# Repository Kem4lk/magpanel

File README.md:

# FM6363C 80x40 1/20-scan HUB75E panel - ESP32-S3 driver (deneysel port)

mrcodetastic'in **ESP32-PWM-MatrixPanel-DMA** (MBI5153, ESP32-S3) implementasyonunun
FM6363C cipine portu. Panel: P4 indoor 80x40, 1/20 scan, 74HC138 satir decode,
FM6363C S-PWM surucu. Register degerleri panelin fabrika .ssx profilinden alindi.

## Mimari
- **LCD peripheral (DMA)**: DCLK + 6 RGB SDI hatti + LE/LAT -> grayscale verisi ve komutlar
- **GPSPI2 octal (DMA, sonsuz dongu)**: GCLK + A..E adres hatlari (satir tarama)

## Kablolama (mevcut HUB75 baglantin korunuyor)
| HUB75 | Islev | GPIO |
|-------|-------|------|
| R1 G1 B1 | ust yari SDI | 4, 5, 6 |
| R2 G2 B2 | alt yari SDI | 7, 15, 16 |
| A B C D E | satir adresi | 18, 8, 3, 9, 13 |
| CLK | DCLK | 12 |
| LAT | LE (komut) | 10 |
| OE | **GCLK** | 11 |

## Sensörler ve tam bağlantı şeması
`hardware/` klasöründe koddan üretilen şema (`gen_schematic.py` → `schematic.svg/png`) ve
pin tablosu var: [hardware/README.md](hardware/README.md). HUB75 kablolaması değişmedi;
beş JSUMO modülü ESP'nin SAĞ başlığına takılır (hepsi 3V3 ile beslenir):

| Modül | Pin | GPIO |
|-------|-----|------|
| LDR Sensor Board (3 pin, dijital) | DO | 1 (ADC1) |
| Microphone Sound Sensor (3 pin, dijital) | OUT | 42 |
| KY-040 Mechanic Encoder | CLK / DT / SW | 41 / 40 / 39 |
| DHT11 Temperature & Humidity | OUT | 47 |
| TTP223B Digital Touch | SIG | 21 |

Firmware tarafı (`include/sensors.h`, `include/sensor_logic.h`): enkoder = parlaklık,
enkoder/dokunmatik/çift alkış → uyku-uyan / sonraki uygulama / sonraki galeri / oto parlaklık
(web UI "Sensörler & kontroller" kartından eşlenir, NVS'te kalır); LDR ile oto parlaklık;
"Oda" (sıcaklık/nem/ışık/saat) ve "Ses" (VU) uygulamaları; 1 Hz `S:` telemetri + `/api/sensors`.

**KiCad taşıyıcı kart:** ESP32-S3-DevKitC-1 soketi, 2× 74HCT245 DIP-20 (3.3 → 5 V), üç HUB75E
çıkışı ve sensör başlıkları olan 2 katmanlı PCB. Şematik, PCB, gerber ve BOM koddan üretilir:
[hardware/kicad/README.md](hardware/kicad/README.md).

## Derleme
VS Code + PlatformIO eklentisi. Proje klasorunu ac -> Build -> Upload.
(`platformio.ini` ESP32-S3 DevKitC-1 icin hazir.)

## Test asamalari ve sorun giderme
1. **Duz kirmizi/yesil/mavi dolgular**: Temizse config + veri yolu calisiyor demektir.
   - Panel tamamen karanliksa: once `FM_GCLKS_PER_ROW`'u 148 yap (cift-kenar sayim ihtimali),
     olmadi GCLK frekansini dusur (spi_dma_seg_tx_loop.c).
   - Renkler yer degistirmisse: app_constants.hpp'de R/G/B pinlerini duzelt.
2. **Kose pikselleri**: Dort kose dogru yerde ve dogru renkteyse haritalama tamam.
   - Ust/alt yarilar ters ise R1<->R2 gruplarini degistir.
   - Satirlar 2'serli atliyorsa D ve E pinlerini degistir.
3. **Piksel yurutme**: x=0..79 duzgun soldan saga akmiyorsa izledigi sirayi not et:
   - 16'sarlik bloklar ters siradaysa: `FM6363_REVERSE_CHANNEL_ORDER 1` yap.
   - Daha karmasik bir desen varsa fabrika .ssx LookUpTab remap'ini ekleyecegiz (bende cozumu hazir).

## Bilinen belirsizlikler (ilk testte netlesecek)
- GCLK cift-kenar sayimi: 74 vs 148 GCLK/satir denemesi gerekebilir.
- VSYNC sirasinda GCLK duraklatma zamanlamasi hassas olabilir.
- Kanal sirasi (ch15 ilk mi) panel PCB'sine bagli.

## Guncelleme (OTA) ve tek komutla deploy
- Her panel `GITHUB_AUTO_OTA` ile `releases/latest`'teki `version.txt`'i yoklar; build
  numarasi artmissa `firmware.bin`'i indirip kurar. Kurulum sirasinda panelde **tum
  piksellerden olusan, alttan dolan loading ekrani** gosterilir (`drawOtaLoading`).
- "Yukle/deploy" demek icin: `tools/magpanel-mcp/` altindaki MCP sunucusu (repo kokundeki
  `.mcp.json` ile otomatik kayitli). Claude'a **"yukle"** dediginizde `deploy_update` araci
  CI'yi tetikler; firmware `latest` release'e gider ve internete bagli tum paneller otomatik
  guncellenir. Kurulum: [tools/magpanel-mcp/README.md](tools/magpanel-mcp/README.md).

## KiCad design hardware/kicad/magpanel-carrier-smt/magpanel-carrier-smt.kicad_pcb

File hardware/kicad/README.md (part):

# MagPanel Carrier — KiCad 8 şematik + PCB

ESP32-S3-DevKitC-1'i soketle taşıyan, üç HUB75E çıkışı (P4 tek panel ya da P1.86 1–3 modül)
ve beş JSUMO sensör başlığı olan iki katmanlı taşıyıcı kart. Kasa (`enclosure/generate_case.py`)
ve bağlantı şeması (`hardware/gen_schematic.py`) gibi her şey **koddan üretilir**:
[`gen_carrier.py`](gen_carrier.py). Pin, parça ya da yerleşim değişirse dosyanın başındaki
tabloları düzelt ve yeniden üret. KiCad'de elle yapılan değişiklik bir sonraki üretimde kaybolur.

| | |
|---|---|
| Kart | 100 × 63.5 mm, 2 katman, 1.6 mm FR4, köşelerde 4× M3 |
| İz genişliği | sinyal 0.25 mm, 3V3 0.5 mm, 5 V / VIN 0.8–1.0 mm |
| Kurallar | boşluk ≥ 0.15 mm, via 0.6/0.3 mm, kenar 0.3 mm (JLCPCB standart 2 katman) |
| El lehimi | en küçük parça 0805, el lehimi pedleri, parçalar arası ≥ 0.5 mm (DRC kuralı) |
| GND | iki katmanda döküm + dikiş via'ları |
| Doğrulama | ERC 0, DRC 0 ihlal, 0 bağlanmamış, şematik↔PCB farkı 0 |

Doğrulama satırı `fab` aşamasında her seferinde yeniden kontrol edilir. Biri sıfır değilse
gerber üretilmez.

**Evde yapmak için** iki sürüm var. İkisi de Elegoo Saturn 3 Ultra ile pozlanır ve yazıcıya hazır
`.goo` dosyalarıyla gelir: negatif dry film için `saturn3/`, Positiv 20 gibi pozitif lak için
`saturn3-pozitif/`.
- Tek yüz, 150 × 100 mm: yalnız alt bakır, tek pozlama, bakır yüzde 3 tel. DevKit pin adları
  soket sıralarının iç tarafında bakırda yazılı. Anlatım: [`TEK-YUZ.md`](TEK-YUZ.md).
- Çift yüz, 100 × 63.5 mm: kaplamasız delik, SMD'ler altta, 33 telli via. Anlatım:
  [`DIY.md`](DIY.md).
- Yalnız SMD, tek yüz, 150 × 100 mm, **delik yok**: bütün parçalar bakır yüzde; UV lehim maskesi,
  reçine macun stencil'i, yerleştirme şablonu, ısıtıcı tabla. Tel yok, bir 0 Ω köprü. Anlatım:
  [`SMT.md`](SMT.md).

## Dosyalar
| Yol | İçerik |
|---|---|
| `magpanel-carrier/` | KiCad 8 projesi: `.kicad_pro`, `.kicad_sch`, `.kicad_pcb`, `.kicad_dru` |
| `magpanel-carrier/MagPanel.kicad_sym`, `MagPanel.pretty/` | DevKit sembolü ve soket footprint'i |
| `fab/magpanel-carrier-gerber.zip` | gerber + delik dosyaları (doğrudan yüklenir) |
| `fab/magpanel-carrier-bom.csv` | tam malzeme listesi |
| `fab/magpanel-carrier-jlc-bom.csv`, `fab/magpanel-carrier-jlc-cpl.csv` | JLCPCB SMT montajı (yalnız SMD, LCSC numaralı) |
| `fab/magpanel-carrier-robotistan-bom.xlsx`, `fab/magpanel-carrier-robotistan-pnp.xlsx` | Robotistan SMT montajı (yalnız SMD, LCSC numaralı) |
| `fab/magpanel-carrier-bomlist.xlsx` | Türkçe BOM şablonu: Fabrika Kodu, Açıklama, Designatör, Malzeme Kılıfı, Adet (yalnız SMD) |
| `fab/magpanel-carrier-schematic.pdf` | şematik (A3) |
| `fab/magpanel-carrier-1to1.pdf` | 1:1 yerleşim testi (A4, ölçek çubuklu) |
| `magpanel-carrier-ss/`, `fab-ss/` | ev yapımı tek yüz sürüm, 150 × 100 mm, bkz. [`TEK-YUZ.md`](TEK-YUZ.md) |
| `magpanel-carrier-diy/`, `fab-diy/` | ev yapımı çift yüz sürüm, bkz. [`DIY.md`](DIY.md) |
| `magpanel-carrier-smt/`, `fab-smt/` | ev yapımı yalnız SMD sürüm, deliksiz, bkz. [`SMT.md`](SMT.md); kodu `smt_variant.py` |
| `img/` | şematik ve kart görselleri |

Şematik: [`img/schematic.png`](img/schematic.png) · Alt yüz: [`img/pcb-bottom.png`](img/pcb-bottom.png)

## Devre
1. **5 V giriş ve koruma.** Vida klemensi J1, 1.5 A PTC sigorta F1 ve SMAJ5.0A TVS D1'den
   geçer. Ters kutupta D1 iletir ve F1 açar. Ardından 470 µF + 10 µF ile DevKit'in **5V**
   pinine ve tamponlara gider. Panel gücü bu karttan geçmez: PSU'dan panele kalın kablo.
   Kartın kendi tüketimi 1 A'in altındadır.
2. **DevKit soketi U1.** İki adet 1×22 dişi soket. Sağ sıra 1.0" (25.40 mm) uzakta: eldeki
   N16R8 klonu (2× USB-C) 1:1 baskı testinde bu sıraya oturdu. Resmi Espressif kartı 0.9"
   (22.86 mm) kullanır; onun için `DEVKIT_RIGHT_ROWS` değiştirilip yeniden üretilir. Anten
   kartın üst kenarından dışarı taşar, USB alt kenardadır.
3. **Seviye dönüştürücü.** İki CD74HCT245E (DIP-20, soketli), 3.3 V mantığı 5 V'a çevirir
   (DIR = 5 V, /OE = GND). HCT girişleri TTL eşiklidir, 3.3 V yüksek seviyeyi 5 V beslemede
   güvenle okur; düz 74HC245 bu iş için uygun değildir. A pinleri DevKit pinleriyle aynı
   2.54 mm adımda, bir iki satır kayarak kısa ve kesişmeyen izlerle bağlanır.
   LAT, LAT2, LAT3 ve OE'de 10 kΩ pull-down var: açılışta GPIO'lar sürülmezken panel karanlık
   kalır. P4'te OE hattı GCLK taşır, P1.86'da aktif-yüksek OE darbesi.
4. **HUB75E çıkışları J2–J4.** Her hatta bir 33 Ω seri direnç (R10–R25, 0805) kablo
   yansımalarını bastırır. Dirençler tek sütundadır, her biri kendi tampon pininin hizasında.
   Bütün hatlar paraleldir, yalnız LAT panel başına ayrıdır:

   | Konnektör | LAT | Kullanım |
   |---|---|---|
   | J2 PANEL 1 | IO10 | P4 ve P1.86 |
   | J3 PANEL 2 | IO17 | yalnız çoklu P1.86 |
   | J4 PANEL 3 | IO14 | yalnız çoklu P1.86 |

5. **Sensör başlıkları (3.3 V).** Pin sırası eldeki JSUMO modüllerinin baskısıyla aynıdır,
   düz kablo çaprazlamaz. GPIO'lar `include/sensors.h` ile aynıdır, her pin serigrafide yazılıdır.

   | Başlık | Modül baskısı | Kart sırası | GPIO |
   |---|---|---|---|
   | J5 LDR | VCC GND DO | 3V3, GND, DO | DO → IO1 |
   | J6 MIC | OUT GND VCC | DO, GND, 3V3 | OUT → IO42 |
   | J7 ENC | CLK DT SW + GND | CLK, DT, SW, 3V3, GND | IO41 / IO40 / IO39 |
   | J8 DHT | − OUT + | GND, DAT, 3V3 | OUT → IO47 |
   | J9 TOUCH | SIG VCC GND | OUT, 3V3, GND | SIG → IO21 |
   | J10 EXP | | 3V3, GND, IO43, IO44, IO38 | genişleme |

   LDR ve mikrofon modülleri yalnız dijital çıkışlıdır. LDR'nin DO'su IO1'den okunur ve oto
   parlaklık iki kademe çalışır. Mikrofonun OUT'u IO42 kesmesine gider. Analog mikrofon girişi
   IO2 boşta gürültü okumasın diye R7 (10 kΩ) onu GND'ye çeker. C5–C7 enkoder için RC filtre,
   R6 DHT11 veri hattı pull-up'ıdır.

GPIO tablosu ve modül notları: [`../README.md`](../README.md).

## Yeniden üretmek
Gerekenler: KiCad 8 (`pcbnew` python modülü ve `kicad-cli`), Java 21+ (Freerouting için),
görseller için Chromium ya da Chrome (`CHROME=/yol` ile verilebilir).

```bash
cd hardware/kicad
PY=/usr/bin/python3        # Linux: KiCad'in python'u
# macOS: PY=/Applications/KiCad/KiCad.app/Contents/Frameworks/Python.framework/Versions/Current/bin/python3
$PY gen_carrier.py sch     # şematik + proje + semboller (yalnız stdlib)
$PY gen_carrier.py pcb     # yerleşim, kart çerçevesi, kilitli 5 V ana hat, SMD GND via'ları
$PY gen_carrier.py route   # Freerouting 2.1.0 + GND dökümü + dikiş via'ları
$PY gen_carrier.py fab     # ERC/DRC kapısı + gerber/delik/BOM/CPL/PDF + görseller
$PY gen_carrier.py all     # hepsi sırayla
$PY gen_carrier.py --ss all    # ev yapımı tek yüz: magpanel-carrier-ss/ ve fab-ss/ (TEK-YUZ.md)
$PY gen_carrier.py --diy all   # ev yapımı çift yüz: magpanel-carrier-diy/ ve fab-diy/ (DIY.md)
$PY gen_carrier.py --smt all   # yalnız SMD: magpanel-carrier-smt/ ve fab-smt/ (SMT.md)
```

- `route` Freerouting jar'ını yoksa `work/` altına indirir (yaklaşık 67 MB).
- Freerouting deterministik değildir: her çalıştırma farklı ama eşdeğer bir yönlendirme
  verir. Aşama, DRC temiz çıkana kadar en çok 10 kez dener. Freerouting bağlantıyı tamam
  sayıp KiCad kopuk görürse mevcut izlerle bir tamamlama turu daha çalışır.
- `work/` ara dosyalar içindir ve git'e girmez.

## Sipariş ve montaj
- **PCB:** `fab/magpanel-carrier-gerber.zip` yükle. 2 katman, 1.6 mm, HASL ya da ENIG.
- **Önce 1:1 test:** `fab/magpanel-carrier-1to1.pdf` dosyasını yazıcıda %100 ölçekle bas,
  alttaki 100 mm çizgiyi cetvelle doğrula, gerçek parçaları deliklere oturt.
- **SMT montaj (isteğe bağlı):** bütün SMD parçalar üst yüzdedir. Montaj dosyalarında yalnız
  bunlar var (33 parça, 8 satır); delikli parçalar elle lehimlenir. Koordinatlar kartın sol-alt
  köşesine göredir, gerber ve delik dosyaları da aynı orijini kullanır. Parçaların LCSC
  numaraları `gen_carrier.py` içindeki `SMT_PARTS` tablosundadır ve LCSC'de stoklu olarak
  doğrulandı (2026-10-02). Yönler KiCad'den gelir: yerleşim önizlemesinde D1'in katot bandı
  sağda (+5V), D2'nin katodu solda (GND) olmalı.
  - JLCPCB: `jlc-bom.csv` ve `jlc-cpl.csv`.
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
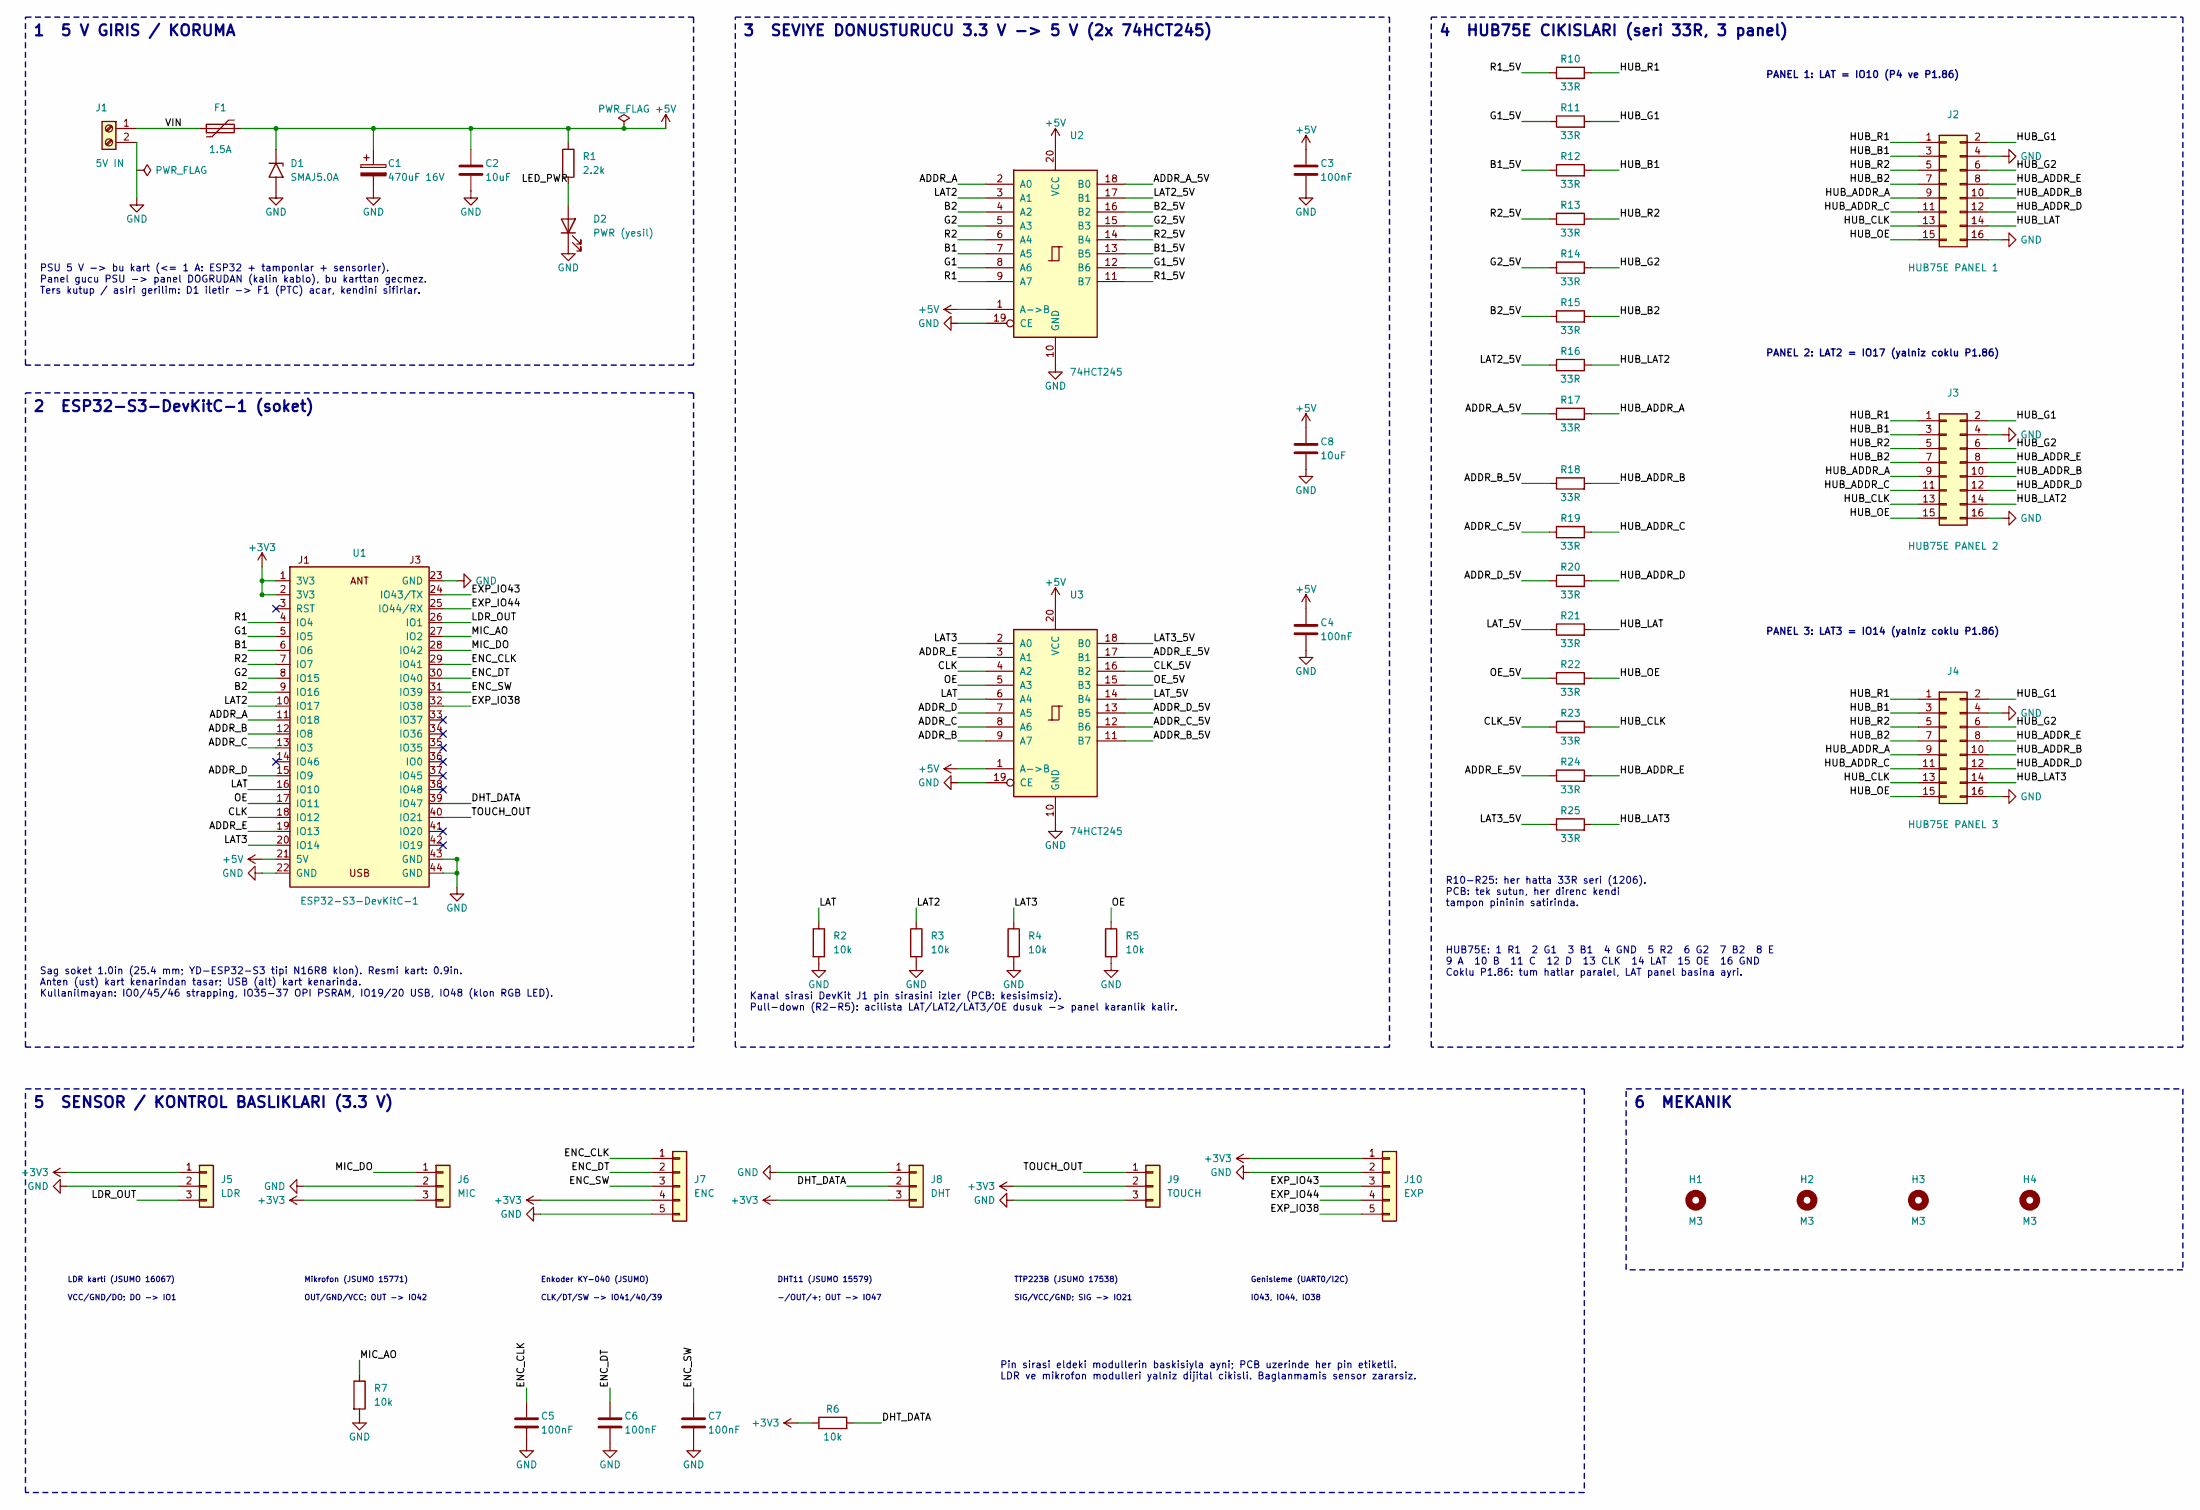
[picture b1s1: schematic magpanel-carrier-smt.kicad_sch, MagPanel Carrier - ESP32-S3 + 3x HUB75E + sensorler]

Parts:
C1: 470uF 16V; CP_Elec_8x10.5; MPN SMD elektrolitik 470 uF 16 V, 8 x 10.5 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
C2, C8: 10uF; C_1206_3216Metric; MPN CL31A106KAHNNNE
C3, C4, C5, C6, C7: 100nF; C_1206_3216Metric; MPN CC1206KRX7R9BB104
D1: SMAJ5.0A; D_SMA; MPN SMAJ5.0A; LCSC C83329
D2: PWR (yesil); LED_1206_3216Metric; MPN KT-1206G
F1: 1.5A; Fuse_1812_4532Metric; MPN MF-MSMF150-2; LCSC C89648
H1, H2, H3, H4: M3; MountMark_M3
J1: 5V IN; BarrelJack_PJ-036AH-SMT; MPN DC jak 5.5 x 2.1 mm SMD (CUI PJ-036AH-S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
J2: HUB75E PANEL 1; IDC-Header_2x08_P2.54mm_Vertical_SMD; MPN SMD kutu baslik (box header) 2x8 2.54 m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
J3: HUB75E PANEL 2; IDC-Header_2x08_P2.54mm_Vertical_SMD; MPN SMD kutu baslik (box header) 2x8 2.54 m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
J4: HUB75E PANEL 3; IDC-Header_2x08_P2.54mm_Vertical_SMD; MPN SMD kutu baslik (box header) 2x8 2.54 m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
J5: LDR; PinHeader_1x03_P2.54mm_SMD; MPN SMD pin header 1x3 2.54 mm erkek
J6: MIC; PinHeader_1x03_P2.54mm_SMD; MPN SMD pin header 1x3 2.54 mm erkek
J7: ENC; PinHeader_1x05_P2.54mm_SMD; MPN SMD pin header 1x5 2.54 mm erkek
J8: DHT; PinHeader_1x03_P2.54mm_SMD; MPN SMD pin header 1x3 2.54 mm erkek
J9: TOUCH; PinHeader_1x03_P2.54mm_SMD; MPN SMD pin header 1x3 2.54 mm erkek
J10: EXP; PinHeader_1x05_P2.54mm_SMD; MPN SMD pin header 1x5 2.54 mm erkek
R1: 2.2k; R_1206_3216Metric; MPN 1206W4J0222T5E
R2, R3, R4, R5, R6, R7: 10k; R_1206_3216Metric; MPN 1206W4J0103T5E
R10, R11, R12, R13, R14, R15, R16, R17, R18, R19, R20, R21, R22, R23, R24, R25: 33R; R_1206_3216Metric; MPN 1206W4J0330T5E
U1: ESP32-S3-DevKitC-1; ESP32-S3-DevKitC-1_SMD; MPN ESP32-S3 N16R8 klon (siralar arasi 1.0i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
U2, U3: 74HCT245; SOIC-20W_7.5x12.8mm_P1.27mm; MPN SN74HCT245DWR / 74HCT245D (SOIC-20W)

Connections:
+3V3: J5.1, J6.3, J7.4, J8.3, J9.2, J10.1, R6.1, U1.1 (3V3), U1.2 (3V3); also elsewhere on the board
+5V: C1.1, C2.1, C3.1, C4.1, C8.1, D1.1 (A1), F1.2, R1.1, U1.21 (5V), U2.1 (A->B), U2.20 (VCC), U3.1 (A->B), U3.20 (VCC)
/ADDR_A: U1.11 (IO18), U2.2 (A0)
/ADDR_A_5V: R17.1, U2.18 (B0)
/ADDR_B: U1.12 (IO8), U3.9 (A7)
/ADDR_B_5V: R18.1, U3.11 (B7)
/ADDR_C: U1.13 (IO3), U3.8 (A6)
/ADDR_C_5V: R19.1, U3.12 (B6)
/ADDR_D: U1.15 (IO9), U3.7 (A5)
/ADDR_D_5V: R20.1, U3.13 (B5)
/ADDR_E: U1.19 (IO13), U3.3 (A1)
/ADDR_E_5V: R24.1, U3.17 (B1)
/B1: U1.6 (IO6), U2.7 (A5)
/B1_5V: R12.1, U2.13 (B5)
/B2: U1.9 (IO16), U2.4 (A2)
/B2_5V: R15.1, U2.16 (B2)
/CLK: U1.18 (IO12), U3.4 (A2)
/CLK_5V: R23.1, U3.16 (B2)
/DHT_DATA: J8.2, R6.2, U1.39 (IO47)
/ENC_CLK: C5.1, J7.1, U1.29 (IO41)
/ENC_DT: C6.1, J7.2, U1.30 (IO40)
/ENC_SW: C7.1, J7.3, U1.31 (IO39)
/EXP_IO38: J10.5, U1.32 (IO38)
/EXP_IO43: J10.3, U1.24 (IO43/TX)
/EXP_IO44: J10.4, U1.25 (IO44/RX)
/G1: U1.5 (IO5), U2.8 (A6)
/G1_5V: R11.1, U2.12 (B6)
/G2: U1.8 (IO15), U2.5 (A3)
/G2_5V: R14.1, U2.15 (B3)
/HUB_ADDR_A: J2.9, J3.9, J4.9, R17.2
/HUB_ADDR_B: J2.10, J3.10, J4.10, R18.2
/HUB_ADDR_C: J2.11, J3.11, J4.11, R19.2
/HUB_ADDR_D: J2.12, J3.12, J4.12, R20.2
/HUB_ADDR_E: J2.8, J3.8, J4.8, R24.2
/HUB_B1: J2.3, J3.3, J4.3, R12.2
/HUB_B2: J2.7, J3.7, J4.7, R15.2
/HUB_CLK: J2.13, J3.13, J4.13, R23.2
/HUB_G1: J2.2, J3.2, J4.2, R11.2
/HUB_G2: J2.6, J3.6, J4.6, R14.2
/HUB_LAT: J2.14, R21.2
/HUB_LAT2: J3.14, R16.2
/HUB_LAT3: J4.14, R25.2
/HUB_OE: J2.15, J3.15, J4.15, R22.2
/HUB_R1: J2.1, J3.1, J4.1, R10.2
/HUB_R2: J2.5, J3.5, J4.5, R13.2
/LAT: R2.1, U1.16 (IO10), U3.6 (A4)
/LAT2: R3.1, U1.10 (IO17), U2.3 (A1)
/LAT2_5V: R16.1, U2.17 (B1)
/LAT3: R4.1, U1.20 (IO14), U3.2 (A0)
/LAT3_5V: R25.1, U3.18 (B0)
/LAT_5V: R21.1, U3.14 (B4)
/LDR_OUT: J5.3, U1.26 (IO1)
/LED_PWR: D2.2 (A), R1.2
/MIC_AO: R7.1, U1.27 (IO2)
/MIC_DO: J6.1, U1.28 (IO42)
/OE: R5.1, U1.17 (IO11), U3.5 (A3)
/OE_5V: R22.1, U3.15 (B3)
/R1: U1.4 (IO4), U2.9 (A7)
/R1_5V: R10.1, U2.11 (B7)
/R2: U1.7 (IO7), U2.6 (A4)
/R2_5V: R13.1, U2.14 (B4)
/TOUCH_OUT: J9.1, U1.40 (IO21)
/VIN: F1.1, J1.1
GND: C1.2, C2.2, C3.2, C4.2, C5.2, C6.2, C7.2, C8.2, D1.2 (A2), D2.1 (K), J1.2, J2.4, J2.16, J3.4, J3.16, J4.4, J4.16, J5.2, J6.2, J7.5, J8.1, J9.3, J10.2, R2.2, R3.2, R4.2, R5.2, R7.2, U1.22 (GND), U1.23 (GND), U1.43 (GND), U1.44 (GND), U2.10 (GND), U2.19 (CE), U3.10 (GND), U3.19 (CE)

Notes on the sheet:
1 5 V GIRIS / KORUMA
PSU 5 V -> bu kart (<= 1 A: ESP32 + tamponlar + sensorler). Panel gucu PSU -> panel DOGRUDAN (kalin kablo), bu karttan gecmez. Ters kutup / asiri gerilim: D1 iletir -> F1 (PTC) acar, kendini sifirlar.
2 ESP32-S3-DevKitC-1 (soket)
Sag soket 1.0in (25.4 mm; YD-ESP32-S3 tipi N16R8 klon). Resmi kart: 0.9in. Anten (ust) kart kenarindan tasar; USB (alt) kart kenarinda. Kullanilmayan: IO0/45/46 strapping, IO35-37 OPI PSRAM, IO19/20 USB, IO48 (klon RGB LED).
3 SEVIYE DONUSTURUCU 3.3 V -> 5 V (2x 74HCT245)
Kanal sirasi DevKit J1 pin sirasini izler (PCB: kesisimsiz). Pull-down (R2-R5): acilista LAT/LAT2/LAT3/OE dusuk -> panel karanlik kalir.
4 HUB75E CIKISLARI (seri 33R, 3 panel)
R10-R25: her hatta 33R seri (1206). PCB: tek sutun, her direnc kendi tampon pininin satirinda.
PANEL 1: LAT = IO10 (P4 ve P1.86)
PANEL 2: LAT2 = IO17 (yalniz coklu P1.86)
PANEL 3: LAT3 = IO14 (yalniz coklu P1.86)
HUB75E: 1 R1 2 G1 3 B1 4 GND 5 R2 6 G2 7 B2 8 E 9 A 10 B 11 C 12 D 13 CLK 14 LAT 15 OE 16 GND Coklu P1.86: tum hatlar paralel, LAT panel basina ayri.
5 SENSOR / KONTROL BASLIKLARI (3.3 V)
LDR karti (JSUMO 16067)
VCC/GND/DO; DO -> IO1
Mikrofon (JSUMO 15771)
OUT/GND/VCC; OUT -> IO42
Enkoder KY-040 (JSUMO)
CLK/DT/SW -> IO41/40/39
DHT11 (JSUMO 15579)
-/OUT/+; OUT -> IO47
TTP223B (JSUMO 17538)
SIG/VCC/GND; SIG -> IO21
Genisleme (UART0/I2C)
IO43, IO44, IO38
Pin sirasi eldeki modullerin baskisiyla ayni; PCB uzerinde her pin etiketli. LDR ve mikrofon modulleri yalniz dijital cikisli. Baglanmamis sensor zararsiz.
6 MEKANIK

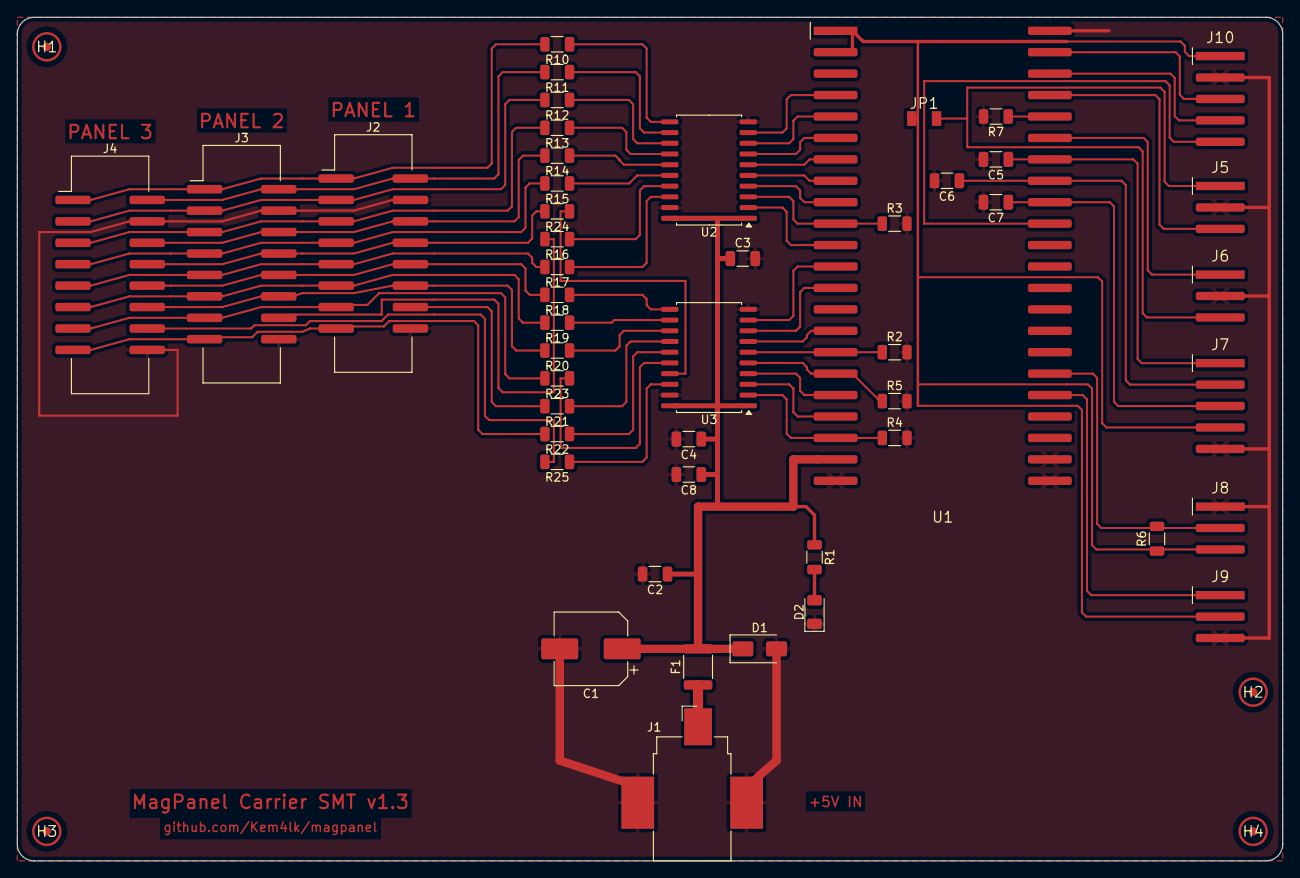
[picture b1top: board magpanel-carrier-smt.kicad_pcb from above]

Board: 2 copper layers, 150.0 x 100.0 mm, 52 parts (0 on the bottom side), 64 nets.

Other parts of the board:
JP1: 0R; Bridge_0R_1206

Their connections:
+3V3: JP1.1, JP1.2; also elsewhere on the board

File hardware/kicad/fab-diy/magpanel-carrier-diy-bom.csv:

Ref,Adet,Deger,Footprint,Montaj,Uretici,Parca / MPN,LCSC,Not
C1,1,470uF 10V,CP_Radial_D8.0mm_P3.50mm,THT,,"Elektrolitik 470 uF 10 V, D8 P3.5 (low ESR)",,"5 V giris tamponu (kablo enduktansi, tampon anahtarlama akimlari)"
C2,1,10uF,C_0805_2012Metric_Pad1.18x1.45mm_HandSolder,SMD,Samsung,CL21A106KAYNNNE,C15850,5 V giris seramik dekuplaj
C3 C4,2,100nF,C_0805_2012Metric_Pad1.18x1.45mm_HandSolder,SMD,YAGEO,CC0805KRX7R9BB104,C49678,74HCT245 VCC dekuplaj (pin 20 yaninda)
C5 C6 C7,3,100nF,C_0805_2012Metric_Pad1.18x1.45mm_HandSolder,SMD,YAGEO,CC0805KRX7R9BB104,C49678,Enkoder RC debounce (modul 10k + 100nF ~ 1 ms)
C8,1,10uF,C_0805_2012Metric_Pad1.18x1.45mm_HandSolder,SMD,Samsung,CL21A106KAYNNNE,C15850,Tamponlar icin yerel 5 V yigin kapasitesi
D1,1,SMAJ5.0A,D_SMA_Handsoldering,SMD,Littelfuse,SMAJ5.0A,C83329,TVS: ters kutup/asiri gerilimde iletir -> F1 acar
D2,1,PWR (yesil),LED_0805_2012Metric_Pad1.15x1.40mm_HandSolder,SMD,Hubei KENTO,KT-0805G,C2297,5 V var gostergesi
F1,1,1.5A,Fuse_1812_4532Metric_Pad1.30x3.40mm_HandSolder,SMD,BOURNS,MF-MSMF150-2,C89648,Kendini sifirlayan sigorta: asiri akim / ters kutupta (D1 iletir) acar
J1,1,5V IN,"TerminalBlock_Phoenix_MKDS-1,5-2-5.08_1x02_P5.08mm_Horizontal",THT,,"Phoenix MKDS 1,5/2-5,08 (1714955) ya da esdegeri",,5 V DC giris (PSU). Panel gucu PSU -> panel dogrudan; bu kart <= 1 A ceker.
J2,1,HUB75E PANEL 1,IDC-Header_2x08_P2.54mm_Vertical,THT,,"Kutu baslik (box header) 2x8 2.54 mm, duz",,HUB75E panel cikisi: LAT = IO10 (P4 ve P1.86)
J3,1,HUB75E PANEL 2,IDC-Header_2x08_P2.54mm_Vertical,THT,,"Kutu baslik (box header) 2x8 2.54 mm, duz",,HUB75E panel cikisi: LAT2 = IO17 (yalniz coklu P1.86)
J4,1,HUB75E PANEL 3,IDC-Header_2x08_P2.54mm_Vertical,THT,,"Kutu baslik (box header) 2x8 2.54 mm, duz",,HUB75E panel cikisi: LAT3 = IO14 (yalniz coklu P1.86)
J5,1,LDR,PinHeader_1x03_P2.54mm_Vertical,THT,,Pin header 1x3 2.54 mm erkek (Dupont),,LDR karti (JSUMO 16067) - VCC/GND/DO; DO -> IO1
J6,1,MIC,PinHeader_1x03_P2.54mm_Vertical,THT,,Pin header 1x3 2.54 mm erkek (Dupont),,Mikrofon (JSUMO 15771) - OUT/GND/VCC; OUT -> IO42
J7,1,ENC,PinHeader_1x05_P2.54mm_Vertical,THT,,Pin header 1x5 2.54 mm erkek (Dupont),,Enkoder KY-040 (JSUMO) - CLK/DT/SW -> IO41/40/39
J8,1,DHT,PinHeader_1x03_P2.54mm_Vertical,THT,,Pin header 1x3 2.54 mm erkek (Dupont),,DHT11 (JSUMO 15579) - -/OUT/+; OUT -> IO47
J9,1,TOUCH,PinHeader_1x03_P2.54mm_Vertical,THT,,Pin header 1x3 2.54 mm erkek (Dupont),,TTP223B (JSUMO 17538) - SIG/VCC/GND; SIG -> IO21
J10,1,EXP,PinHeader_1x05_P2.54mm_Vertical,THT,,Pin header 1x5 2.54 mm erkek (Dupont),,"Genisleme (UART0/I2C) - IO43, IO44, IO38"
R1,1,2.2k,R_0805_2012Metric_Pad1.20x1.40mm_HandSolder,SMD,UNI-ROYAL,0805W8F2201T5E,C17520,PWR LED akim siniri (~1 mA)
R2 R3 R4 R5,4,10k,R_0805_2012Metric_Pad1.20x1.40mm_HandSolder,SMD,UNI-ROYAL,0805W8F1002T5E,C17414,Pull-down: acilista GPIO surulmezken LAT/OE dusuk -> panel karanlik
R6,1,10k,R_0805_2012Metric_Pad1.20x1.40mm_HandSolder,SMD,UNI-ROYAL,0805W8F1002T5E,C17414,DHT11 DATA pull-up (ciplak sensor icin; modul uzerindekiyle paralel sorun degil)
R7,1,10k,R_0805_2012Metric_Pad1.20x1.40mm_HandSolder,SMD,UNI-ROYAL,0805W8F1002T5E,C17414,IO2 (analog mikrofon girisi) bosta gurultu okumasin: eldeki mikrofon modulu yalniz dijital
R10 R11 R12 R13 R14 R15 R16 R17 R18 R19 R20 R21 R22 R23 R24 R25,16,33R,R_0805_2012Metric_Pad1.20x1.40mm_HandSolder,SMD,UNI-ROYAL,0805W8F330JT5E,C17634,Seri sonlandirma: kablo yansimalarini/zil (ringing) bastirir
U1,1,ESP32-S3-DevKitC-1,ESP32-S3-DevKitC-1_Socket,THT,,"ESP32-S3 N16R8 klon (YD-ESP32-S3 tipi, siralar arasi 1.0in) + 2x 1x22 disi soket (2.54 mm)",,"ESP32-S3-DevKitC-1 uyumlu gelistirme karti (eldeki: N16R8 klon, 2x USB-C); 2x22 disi soket. Sag sira 1.0in (25.4 mm); resmi Espressif karti 0.9in."
U2 U3,2,74HCT245,DIP-20_W7.62mm_Socket_LongPads,THT,,CD74HCT245E (PDIP-20) + 20 pin DIP soket,,"Octal bus transceiver, HCT = TTL girisli (3.3 V mantik 5 V beslemede gecerli); DIR=+5V (A->B), /OE=GND"

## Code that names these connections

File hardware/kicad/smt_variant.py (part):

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    for y in (y34b, g(6) - 0.17):
        out.append(('+3V3', [(xin, y), (xo, y)], 0.25))
    # IO38 halkası
    out.append(('EXP_IO38', [(xi, pin_y(10)), (IO38_X, pin_y(10)), (IO38_X, y34a), (xo, y34a)], W))
    # dış taraf: sağ sıra -> başlıklar (merdiven, sağa)
    hp = lambda ref, k: pad(ref, str(k))
    tx = SENS_X - 2.3
    sens = [('+3V3', g(1), hp('J10', 1)), ('EXP_IO43', pin_y(2), hp('J10', 3)), ('EXP_IO44', pin_y(3), hp('J10', 4)),
            ('EXP_IO38', y34a, hp('J10', 5)), ('+3V3', y34b, hp('J5', 1)), ('LDR_OUT', pin_y(4), hp('J5', 3)),
            ('MIC_DO', pin_y(6), hp('J6', 1)), ('+3V3', g(6) - 0.17, hp('J6', 3)), ('ENC_CLK', pin_y(7), hp('J7', 1)),
            ('ENC_DT', pin_y(8), hp('J7', 2)), ('ENC_SW', pin_y(9), hp('J7', 3)), ('+3V3', yb[0], hp('J7', 4)),
            ('DHT_DATA', pin_y(17), hp('J8', 2)), ('+3V3', yb[1], hp('J8', 3)), ('TOUCH_OUT', pin_y(18), hp('J9', 1)),
            ('+3V3', yb[2], hp('J9', 2))]
    lines = [('%d' % k, (xo, y), (tx, t[1])) for k, (n, y, t) in enumerate(sens)]
    # LDR-MIC, CLK-DT, DT-SW, SW-3V3 arasında döküm geçer: IO38 halkasının içindeki R7, C5-C7 GND'si buradan
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
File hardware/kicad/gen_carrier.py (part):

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        return str(DEVKIT_J1.index(name) + 1)
    return str(DEVKIT_J3.index(name) + 23)

# HUB75: ESP GPIO -> sinyal (include/app_constants.hpp; LAT2/LAT3 panel_sm16380.h)
HUB_GPIO = {
    'R1': 'IO4', 'G1': 'IO5', 'B1': 'IO6', 'R2': 'IO7', 'G2': 'IO15', 'B2': 'IO16',
    'ADDR_A': 'IO18', 'ADDR_B': 'IO8', 'ADDR_C': 'IO3', 'ADDR_D': 'IO9', 'ADDR_E': 'IO13',
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# pin 1 tampon tarafi (*_5V), pin 2 konnektor tarafi (HUB_*). (ref, sinyal, DevKit satiri)
SERIES_R = ([('R%d' % (10 + k), sig, 2 + k) for k, sig in enumerate(reversed(BUF_CH['U2']))] +
            [('R%d' % (18 + k), sig, 13 + k) for k, sig in enumerate(reversed(BUF_CH['U3']))])
# HUB75E konnektor pinleri (standart). 14 = LAT (panel basina ayri).
HUB_PINS = {1: 'R1', 2: 'G1', 3: 'B1', 4: 'GND', 5: 'R2', 6: 'G2', 7: 'B2', 8: 'ADDR_E',
            9: 'ADDR_A', 10: 'ADDR_B', 11: 'ADDR_C', 12: 'ADDR_D', 13: 'CLK', 14: None,
            15: 'OE', 16: 'GND'}
HUB_CONN = [('J2', 'LAT', 'PANEL 1', 'LAT = IO10 (P4 ve P1.86)'),
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    ('J9', 'TOUCH', [('OUT', 'TOUCH_OUT'), ('3V3', '+3V3'), ('GND', 'GND')], 'TTP223B (JSUMO 17538) - SIG/VCC/GND; SIG -> IO21'),
    ('J10', 'EXP', [('3V3', '+3V3'), ('GND', 'GND'), ('IO43', 'EXP_IO43'), ('IO44', 'EXP_IO44'), ('IO38', 'EXP_IO38')], 'Genisleme (UART0/I2C) - IO43, IO44, IO38'),
]
SENSOR_GPIO = {'LDR_OUT': 'IO1', 'MIC_AO': 'IO2', 'MIC_DO': 'IO42', 'ENC_CLK': 'IO41', 'ENC_DT': 'IO40',
               'ENC_SW': 'IO39', 'DHT_DATA': 'IO47', 'TOUCH_OUT': 'IO21', 'EXP_IO43': 'IO43/TX',
               'EXP_IO44': 'IO44/RX', 'EXP_IO38': 'IO38'}
ENC_CAPS = [('C5', 'ENC_CLK'), ('C6', 'ENC_DT'), ('C7', 'ENC_SW')]
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                   desc='5 V var gostergesi')
    ra = r1.pin(2); la = d2.pin(2)
    sch.wire((ra[0], ra[1]), (la[0], la[1]))
    sch.label('LED_PWR', ra[0], ra[1], (-1, 0))
    sch.assign(r1, 2, 'LED_PWR'); sch.assign(d2, 2, 'LED_PWR')
    sch.pwr(d2, 1, 'GND', length=0)
    sch.text('PSU 5 V -> bu kart (<= 1 A: ESP32 + tamponlar + sensorler).\n'
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    for i, (ref, net) in enumerate(PULLDOWNS):
        r = sch.place('Device:R', ref, '10k', *P(63 + i * 7, 72.5), footprint=FP['R0805'],
                      ref_at=(2.54, -1.27), val_at=(2.54, 1.27), fields=smt('10k'),
                      desc='Pull-down: acilista GPIO surulmezken LAT/OE dusuk -> panel karanlik')
        x0, y0, _ = r.pin('1')
        sch.wire((x0, y0), (x0, y0 - G))
        sch.label(net, x0, y0 - G, (1, 0))
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                   desc='IO2 (analog mikrofon girisi) bosta gurultu okumasin: eldeki mikrofon modulu yalniz dijital')
    x0, y0, _ = r7.pin('1')
    sch.wire((x0, y0), (x0, y0 - G))
    sch.label('MIC_AO', x0, y0 - G, (1, 0))
    sch.assign(r7, '1', 'MIC_AO')
    sch.pwr(r7, '2', 'GND', length=0)
    r6 = sch.place('Device:R', 'R6', '10k', *P(64, 107), rot=90, footprint=FP['R0805'],
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    for ref, lat, title, note in HUB_CONN:
        x, y, _, _ = PLACE[ref]
        silk_text(board, '%s %s' % (ref, title), x + 1.27, y - 6.6, 0.9)
        silk_text(board, lat + '=' + HUB_GPIO[lat], x + 1.27, y + 24.2, 0.8)
    # sensor basliklari: ad ustte, pin etiketleri solda
    for ref, name, pins, _ in SENSOR_HDRS:
        x, y, _, _ = PLACE[ref]
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SS_SENS_X = 136.0                 # sensor basliklari (dikey, pin 1 ustte): sinyal + 3V3 soldan, GND sagdan
SS_VIA = (1.6, 0.8)               # tel pedi / delik (tel ucu bakir yuzde pede lehimlenir, delmek istege bagli)
SS_VIA_COST = int(os.environ.get('SS_VIA_COST', 120))   # Freerouting via maliyeti: yuksek -> az tel
# Seri 33R sutunu HUB75 serit sirasinda (... D, CLK, LAT, OE). CLK'nin B pini (satir 18) LAT ve OE'nin altinda:
# iz soketin ic koridorundan yukari cikip D ile LAT arasindan sutuna girer (tel gerekmez).
SS_RROW = {'CLK': 16, 'LAT': 17, 'OE': 18}

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    Basliklar 1.27 mm basamakli: baslik arasi izler duz. Seritte sira pin sirasi (1 R1 ... 16 GND); GND (4, 16) son
    basligin otesinde birlesir. Tek katmanda kesismesi kacinilmaz uc hat telle (ust katman = bakir yuzde tel):
    E (sutunun altindan seritteki yerine), LAT2 (seritin icinden J2-J3 arasina), LAT3 (seritin altindan J3-J4
    arasina). Tampon B pinleri -> 33R; CLK soketin ic koridorundan cikip D ile LAT arasindan sutuna girer."""
    import pcbnew
    w, h2 = 0.25, G / 2
    hubs = ['J2', 'J3', 'J4']                          # tamponlara en yakindan en uzaga
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    T = lambda n, pts, layer=pcbnew.B_Cu, width=w: add_track(board, nets[n], pts, width, layer=layer)
    via = lambda n, x, y: add_via(board, nets[n], x, y, SS_VIA[0], SS_VIA[1])
    hubnet = lambda p: 'GND' if HUB_PINS[p] == 'GND' else 'HUB_' + HUB_PINS[p]
    # 1) basliklar arasi ve baslik ici gecis (LAT = pin 14 panel basina ayri, burada yok)
    for p in range(1, 17):
        if p == 14:
            continue
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    # 2) seri 33R (ped 2) -> J2: 45 derece yelpaze, hepsi J2'nin 2 mm onunde duzlesir
    rref = {sig: ref for ref, sig, _ in SERIES_R}
    slot = {sig: p for p, sig in HUB_PINS.items() if sig not in (None, 'GND')}
    slot['LAT'] = 14
    xe = X['J2'] + G + 2.0
    def into_j2(p):                                    # J2'nin onunden pine (tek pin yakin sutun araligindan)
        r = (p - 1) // 2
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    for v in (l3a, l3b):
        via('HUB_LAT3', *v)
    T('HUB_LAT3', [l3a, l3b], layer=pcbnew.F_Cu)
    # 6) tampon B pinleri -> 33R ped 1 (sutun serit sirasinda; LAT ve OE bir satir asagi, CLK soket icinden)
    for ref, sig, brow in SERIES_R:
        u, pin = ('U2', str(brow + 9)) if brow <= 9 else ('U3', str(brow - 2))   # 180 derece: B pin m satir m-9 / m+2
        xb, yb = pad_xy(fps[u], pin)
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        xr, yrr = pad_xy(fps[ref], '1')
        n = sig + '_5V'
        if sig == 'CLK':
            yg = pin_y(brow - 3) + h2                    # D (satir 15) ile LAT (16) B pinleri arasi
            T(n, [(xb, yb), (xb + 1.85, yb), (xb + 1.85, yg), (xr + (yrr - yg), yg), (xr, yrr)])
        elif abs(yrr - yb) < 1e-6:
            T(n, [(xb, yb), (xr, yrr)])
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
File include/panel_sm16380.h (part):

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    (varsayilan 13) yazilir, ustteki bitler 0.

  COKLU PANEL (1..3, ayni ESP32): modulde OUT soketi yok -> zincir yok. Tum paneller
  ayni RGB/DCLK/OE/ABCDE hatlarini paylasir; sadece LE (LAT, HUB75 pin 14) panel
  basina ayri GPIO'dan gelir (P1: GPIO10 = d6, P2: GPIO17 = d13, P3: GPIO14 = d14).
  Veri paylasilan hatta panel panel ardisik akar; bir panelin gri ton verisini yalniz
  kendi LE'si latch'ler, digerleri ayni bitleri kaydirip gecirir ama latch'lemez.
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static_assert(DATA_WORDS % CYCLE_WORDS == 0, "panel verisi tam cevrim olmali (paneller ardisik)");
static_assert(DATA_WORDS % PASS_WORDS == 0, "panel verisi tam gecis olmali");

// Coklu panel: panel basina LE (LAT) hatti. P1 = BIT_LAT (d6, GPIO10, P4 ile ayni kablo).
constexpr int MAX_PANELS = 3;
constexpr int8_t LAT2_PIN = 17;             // d13: 2. panelin HUB75 pin 14'u
constexpr int8_t LAT3_PIN = 14;             // d14: 3. panelin HUB75 pin 14'u
constexpr uint16_t B_LAT2 = (1 << 13);
constexpr uint16_t B_LAT3 = (1 << 14);
enum Layout : uint8_t { LAYOUT_VERTICAL = 0, LAYOUT_HORIZONTAL = 1 };
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    bus_cfg.pin_d3 = MBI_G2;  bus_cfg.pin_d4 = MBI_B2;  bus_cfg.pin_d5 = MBI_R2;
    bus_cfg.pin_d6 = MBI_LAT;
    bus_cfg.pin_d7 = MBI_GCLK;      // HUB75 OE pini
    bus_cfg.pin_d8 = ADDR_A_PIN;  bus_cfg.pin_d9 = ADDR_B_PIN;  bus_cfg.pin_d10 = ADDR_C_PIN;
    bus_cfg.pin_d11 = ADDR_D_PIN; bus_cfg.pin_d12 = ADDR_E_PIN;
    // 2. ve 3. panelin LE hatlari (baglanmamis olsa da surulur: sabit 0)
    bus_cfg.pin_d13 = n_ >= 2 ? LAT2_PIN : -1;
    bus_cfg.pin_d14 = n_ >= 3 ? LAT3_PIN : -1;
    bus_cfg.pin_d15 = -1;
    bus_.config(bus_cfg);
    bus_.setup_lcd_dma_periph();
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
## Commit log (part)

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2026-06-12 v21
    hello v21
2026-06-12 v22 3 files
2026-06-13 sat jun 13 11:00
2026-06-13 main ccp
2026-06-13 main cpp update
2026-06-13 platform update
2026-06-13 web page ve wifi update
2026-06-13 CI: etiket sabitleme adimini hatasiz birak (release pipeline'i bozmasin)
    continue-on-error: latest etiketi itilemezse bile derleme ve release
    adimlari calismaya devam eder.
    https://claude.ai/code/session_01729z8mfuzpDVT8xM73TWmN
2026-06-13 BLE provisioning + local build OTA fix
    - Local builds (FW_BUILD=0) no longer auto-OTA; prevents boot loop when
    CI firmware has wrong WiFi password after a credential change
    - BLE provisioning: if WiFi fails at boot, panel advertises as
    'MagPanel-Setup' over BLE; use nRF Connect to write 'SSID\nPASS' to
    the CRED characteristic; credentials saved to NVS, panel restarts
    - NVS credential priority: NVS (BLE-stored) > compiled wifi_config.h > BLE mode
2026-06-13 Replace BLE provisioning with WiFi AP-mode (fixes matrix DMA crash)
    BLE library reserved enough internal RAM that the HUB75 DMA buffer
    allocation in Matrix::initMatrix() failed (assert dma_grey_gpio_data
    != nullptr) -> boot loop. BLE + WiFi + large LED DMA do not fit
    together on this chip.
    Switch to WiFi AP-mode provisioning instead: on WiFi failure the panel
    serves an open 'MagPanel-Setup' network; user connects, opens
2026-06-13 Add CLAUDE.md with project working notes and open issues
    Captures: secrets/branch constraints, low-heap (~7KB max block) limit,
    fixed bugs (FW_BUILD==0 OTA guard, BLE->AP-mode DMA crash), the open GIF
    web-page JS error with diagnosis steps, flashing workflows (USB/espota/
    web-update), local env quirks (broken ~/.git, apostrophe path, IP hopping
    needing a DHCP reservation), and the WS protocol. No secrets included.
    https://claude.ai/code/session_01729z8mfuzpDVT8xM73TWmN
2026-06-13 index sayfasini PROGMEM'den akitarak gonder (art/ws "is not defined" fix)
    Sorun: "/" handler'i sayfayi FPSTR ile ~9 KB'lik tek bir heap String'e
    kopyalayip (replace + send) gonderiyordu. Bellek baskisi/parcalanma altinda
    yanit yarim gidebiliyor; govde (butonlar) gorunuyor ama sondaki <script>
    blogu kesiliyor. Eksik script parse edilemiyor -> hicbir global tanimlanmiyor
    -> inline handler'lar "art is not defined" / "ws is not defined" firlatiyor.
    (Sayfa HTML/JS'i tam haliyle gecerli; node --check ve jsdom ile dogrulandi.)
2026-06-13 OTA piksel loading ekrani + tek komutla deploy MCP sunucusu
    Loading ekrani (firmware):
    - drawOtaLoading(pct): tum 80x120 paneli kullanan, alttan dolan piksel ilerleme
    cubugu (turuncu dolu, beyaz ilerleme cizgisi, koyu bos).
    - checkGithubOTA artik firmware'i parca parca yaziyor; her parcada cubugu gunceller
    ve arada matrix.refresh() ile paneli yanik tutar (eski writeStream ekrani
    karanlik birakiyordu). Web /update ve espota yollarina da ilerleme eklendi.
2026-06-13 enclosure: difüzör kalınlık test kuponu (0.6-1.5mm, reçine için)
    https://claude.ai/code/session_01Vf3Xh3YCRR4xuW6EnRzPud
2026-06-13 enclosure: test kuponunu genişlet (0.2-1.2mm + düz/çizgili/ızgara doku yamaları)
    https://claude.ai/code/session_01Vf3Xh3YCRR4xuW6EnRzPud
2026-06-13 web UI GIF oynatma duzeltmesi: ImageDecoder.tracks.ready beklenmiyordu
    playGif() 'await dec.completed' yapip 'await dec.tracks.ready' yapmadan
    tracks.selectedTrack.frameCount okuyordu. Iz metadata'si hazir olmadigindan
    frameCount 0/1 gorunuyor -> playGif false donup statik tek-kare yoluna
    dusuyordu (konsol hatasi yok, panel ilk kareyi statik gosteriyor, animasyon
    oynamiyor). Duzeltme: once 'await dec.tracks.ready', sonra 'await dec.completed';
    ayrica selectedTrack null korumasi.
2026-06-13 GIF debug: LOG paneline adim adim teshis mesajlari ekle
    ImageDecoder desteği yok mu, frameCount sifir mi, decode hatasi mi
    oldugu LOG panelinde gorunur. Kullanici F12 acmadan debug edebilir.
    https://claude.ai/code/session_01UawgRsDdLyXXe6JBSbmsXV
2026-06-13 web UI: MP4/video oynatma destegi ekle
    - File input: image/* + video/mp4,webm,quicktime kabul eder
    - playVideo(): HTMLVideoElement + requestAnimationFrame ile her kareyi
    80x120'ye scale edip WS üzerinden panele gonder (loop, muted).
    bufferedAmount<60000 kontrollü, FPS'i WiFi kapasitesine göre otomatik
    sinirlar.
    - stopGif: RAF (video) ve setTimeout (GIF) ikisini de iptal eder
2026-06-13 GitHub OTA manuel buton: WS opcode 0x09
    Web sayfasi footer'ina 'GitHub'dan Guncelle' butonu eklendi.
    Tiklandiktan sonra WS 0x09 gonderilir; cihaz checkGithubOTA()'yi
    tetikler. Guncel ise LOG'a yazar, daha yeni build varsa yukleme
    ekrani + restart yapar.
    https://claude.ai/code/session_01UawgRsDdLyXXe6JBSbmsXV
2026-06-13 Otomatik GitHub OTA kaldirildi, sadece manuel buton
    GITHUB_AUTO_OTA periyodik kontrolu loop()'tan silindi.
    Guncelleme artik yalnizca kullanici 'GitHub'dan Guncelle'
    butonuna bastiktan sonra yapilir. Sayfa beklenmedik anlarda
    kapanmaz.
    https://claude.ai/code/session_01UawgRsDdLyXXe6JBSbmsXV
2026-06-13 GIF fallback: Safari/Firefox icin img+RAF animasyonu
    ImageDecoder olmayan tarayicilarda <img> elementi ile browser
    native GIF animasyonunu render eder, requestAnimationFrame ile
    her kareyi canvas'a cekip panele gonderir. Tum tarayicilarda
    calisir.
    https://claude.ai/code/session_01UawgRsDdLyXXe6JBSbmsXV
2026-06-13 OTA butonu: guncelleme sureci gorseli
    - Tiklandiktan sonra buton 'Kontrol ediliyor...' olur, disable edilir
    - Yeni build bulununca WS kapanir -> buton 'Guncelleniyor...' gosterir
    - Cihaz yeniden baglaninca -> 'Baglandi - yeni firmware aktif!' logu
    - 12 sn icinde WS kapanmazsa 'Guncel, guncelleme yok.' ile resetlenir
    https://claude.ai/code/session_01UawgRsDdLyXXe6JBSbmsXV
2026-06-14 enclosure: piksel-ızgara kasası (80x120 kare göz) + Saturn dizilim
    Görüntü/yazı paneli için her LED kendi 3.2mm kare gözünde (9600 hücre, P4 4mm).
    Kapalı 0.7mm difüzör ön + 0.8mm ızgara duvar = dolu kare pikseller, kontrast.
    2x2 fayans (dikiş ızgara çizgisine denk -> görünmez). Elegoo Saturn 3 Ultra'ya
    DİK basınca 4 fayans tek plakaya sığar (saturn_plate_4tiles_standing.stl).
    - generate_pixel_case.py: parametrik üretici
    - stl_pixel/: 4 fayans + Saturn dizilim STL
2026-06-14 enclosure: piksel kasası tam referans STL (bölünmemiş)
    https://claude.ai/code/session_01Vf3Xh3YCRR4xuW6EnRzPud
2026-06-14 GIF animasyon: gercek JS GIF89a cozucu (Safari/iOS)
    Eski fallback DOM disi <img> elemanini canvas'a ciziyordu; tarayicilar
    DOM disi animasyonlu GIF'i ilerletmez (hep 0. kare) -> Safari/iOS'ta
    animasyon yoktu, ayni kare gonderiliyordu.
    Cozum: LZW + disposal kompoziti yapan tam GIF89a cozucu eklendi.
    Kareler bir kez cozulup 80x120'ye olceklenir, sonra gecikmelerine
    gore sirayla panele gonderilir. ImageDecoder olan tarayicilarda
2026-06-14 GIF gercek-zamanli pacing + DCLK tuner UI
    - GIF oynatma video yoluyla ayni pacing'e gecti: kumulatif zaman cizelgesi,
    <=15fps gonderim, panel/WS yetisemezse kare DUSUR. Eski setTimeout(delay)
    hizli GIF'lerde WS buffer'ini tasirip duzensiz atlamaya yol aciyordu ->
    'cok yavas/takilarak' oynuyordu. Artik gercek-zamanli, telefondaki hizda.
    - Gelismis bolumde DCLK/flicker tuner: 2.0-6.0 MHz butonlari (opcode 0x0A),
    aktif kademe vurgulanir, secim panele kaydedilir. 'En yuksek mozaiksiz hiz'
2026-06-14 DCLK canli tuner: WS 0x0A + NVS + runtime bolen degisimi
    Donanima 'en uygun' DCLK jumper-kablo bus'ina ozgu ve ancak panel uzerinde
    test edilerek bulunur (2.5MHz calisiyor, 7MHz ring->mozaik). Reflash dongusu
    olmadan bulmak icin canli tuner:
    - Bus_Parallel16::set_clock_divider(): LCD_CAM.lcd_clkm_div_num'u calisma
    aninda yazar (loop context, transferler arasi guvenli). div sadece kaydirma
    hizini degistirir; 1/20 scan yapisi (20 satir,74 GCLK,deadtime3) korunur.
2026-06-14 UI: DCLK tuner'a 7.0–10.0 MHz seçenekleri eklendi
    Yeni butonlar: 7.0 (bölücü 23), 8.0 (20), 8.9 (18), 10.0 (16) MHz.
    https://claude.ai/code/session_01UawgRsDdLyXXe6JBSbmsXV
2026-06-14 Uygulamalar: Saat/Timer/Hava/Dunya Kupasi/Spotify (firmware-tarafi render)
    Panel verileri KENDISI ceker (NTP saat, HTTPS hava/skor) ve GFX_Lite ile
    cizer; tarayici gerekmez. Son secilen uygulama NVS'e ("appcfg") kaydedilir ->
    reboot'ta panel tarayicisiz ayni uygulamayla geri gelir.
    - include/apps.h: app framework (Apps sinifi). Saat (NTP, UTC+3), Timer
    (geri sayim), Hava (Open-Meteo, anahtarsiz, WMO kod->Turkce), Dunya Kupasi
    2026 (TheSportsDB, lig ID configurable), Spotify (ISKELET: token tarayici
2026-06-14 fix(apps): CRGB to RGB565 conversion in centerText
    GFX_Lite setTextColor template assigns to uint16_t internally;
    CRGB has no implicit uint16_t conversion. Convert explicitly via
    bit-shift formula before calling setTextColor.
    https://claude.ai/code/session_01UawgRsDdLyXXe6JBSbmsXV
2026-06-14 feat(gallery): 20 kamu malı ünlü tablo eklendi
    Galeriye 20 ek tablo: Büyük Dalga, Kız Küpeli, Son Akşam Yemeği,
    Venüs'ün Doğuşu, Athena Okulu, Özgürlük Rehberi, Gece Nöbeti,
    Uyuyan Venüs, Goya/Kronos, Olympia, Nilüfer Havuzu, Saman Arabası,
    Grande Jatte, Moulin Galette, Persistans, Guernica, Amerikan Gotiği,
    Sistine/Yaratılış, Bahar Bahçesi, İki Frida.
    GALLERY_COUNT: 4 → 24. Tüm diziler PROGMEM'de (flash).
2026-06-14 feat: görüntü ayarlarına blur efekti eklendi
    Opcode 0x0E + 1B (0=kapalı, 1=3×3, 2=5×5, 3=7×7 box blur).
    Blur, renderFrame()'de framebuf üzerinden komşu piksel
    ortalaması alınarak uygulanır — ekstra bellek ayırımı yok.
    Matrix.h'a img_blur alanı eklendi. Web UI'da Doygunluk
    altına Blur kaydırıcısı eklendi (Kapalı/3×3/5×5/7×7).
    https://claude.ai/code/session_01UawgRsDdLyXXe6JBSbmsXV
2026-06-14 feat: galeri dinamik + son gönderilenler bölümü
    - /api/gallery endpoint: GALLERY_NAMES'i JSON olarak döndürür;
    tüm 24 tabloyu otomatik listeler, ileride eklenenler de görünür.
    - Web UI Galeri kartı: fetch('/api/gallery') ile butonları sayfa
    yüklenince oluşturur (hardcode yok).
    - "Son Gönderilenler" kartı: sendFrame() her çağrıldığında canvas
    içeriği PNG olarak localStorage'a kaydedilir (max 8 slot).
2026-06-14 chore(tools): gerçek Wikimedia indirme betiği eklendi
    Mac'te çalıştırmak için: pip3 install Pillow requests
    python3 tools/gen_gallery_real.py
    https://claude.ai/code/session_01UawgRsDdLyXXe6JBSbmsXV
2026-06-14 perf(ui): yüksek kaliteli çok adımlı resim küçültme
    drawImage() direkt büyük→80x120 yerine: önce boyutu her adımda
    yarıya indiren hqScale(), son adımda 80x120'ye imageSmoothingQuality
    ='high' ile çeker. Tek adımlı downscale'deki pikselleşme ve renk
    kayması giderildi. Fotoğraf, video ve GIF yollarının tümüne uygulandı.
    https://claude.ai/code/session_01UawgRsDdLyXXe6JBSbmsXV
2026-06-14 fix(tools): Wikimedia API ile URL al, cover-fit küçültme
2026-06-14 Blur: 2x2 kademesi ekle (daha granuler artis)
    Blur kaydiricisina Kapali ile 3x3 arasina 2x2 ara kademesi eklendi.
    img_blur artik yariçap degil kademe indeksi: 0=kapali, 1=2x2, 2=3x3,
    3=5x5, 4=7x7. 2x2 asimetrik (piksel+sag+alt+sag-alt), digerleri
    simetrik box blur. Web UI slider max=4, etiketler guncellendi.
    https://claude.ai/code/session_01DHsn8W5C13is6RgFUicV4z
